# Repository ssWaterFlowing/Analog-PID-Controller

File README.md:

# Analog PID Controller
### A Fully Analog Closed-Loop LED Brightness Controller

## Project Overview

A **fully analog PID (Proportional-Integral-Derivative) controller** that regulates LED brightness using only op-amp circuits, passive components, and a BJT output driver. No microcontroller, no software, no digital processing. The system senses LED current, computes the error against a setpoint, and drives a corrective output through three parallel analog compensation paths (P, I, D) summed into a single control signal.

Designed as an independent project to physically realize classical control theory in hardware, where gain is set by resistor ratios, time constants by RC products, and stability by circuit topology.

**Authors:** Suren Shirani and Devansh Joshi

## System Architecture

The controller implements a standard closed-loop PID topology in five analog stages:

```
                         ┌──────────────────────────────────────────┐
                         │              PID Compensation            │
                         │                                          │
V_set ──┐                │  ┌─────────────┐                        │
        │  ┌───────────┐ │  │ Proportional │──┐                    │
        ├─►│ Difference ├─┼─►│   (Kp gain)  │  │  ┌─────────────┐  │  ┌────────────┐
        │  │ Amplifier  │ │  ├─────────────┤  ├─►│  Summing     ├──┼─►│  2N3904    ├──► LED
V_curr ─┘  │  (TL082)   │ │  │  Integral   │  │  │  Inverting   │  │  │  BJT       │
           └───────────┘ │  │  (Ki gain)   │──┘  │  Amplifier   │  │  │  Driver    │
              e(t)       │  ├─────────────┤      │  (TL084)     │  │  └────────────┘
                         │  │ Derivative   │──┘  └─────────────┘  │
                         │  │  (Kd gain)   │                       │
                         │  └─────────────┘                        │
                         │      (TL084)                            │
                         └──────────────────────────────────────────┘
                                                                    │
                         ┌──────────────────────────────────────────┘
                         │ Feedback: V_curr = f(I_LED)
                         └─────────────────────────────────────────►V_curr
```

### Signal Flow

1. **Setpoint (V_set):** A calculated reference voltage representing the desired LED operating point
2. **Current Sense (V_curr):** The LED forward voltage is measured directly as a proxy for LED current
3. **Error Computation:** A TL082 difference amplifier computes `e(t) = V_set − V_curr`
4. **PID Compensation:** The error signal is routed in parallel to three TL084-based op-amp stages:
   - **P stage** - Resistor-ratio gain provides immediate proportional correction
   - **I stage** - Op-amp integrator (RC time constant) accumulates past error to eliminate steady-state offset
   - **D stage** - Op-amp differentiator (RC time constant) responds to rate-of-change to reduce overshoot
5. **Summation:** A TL084 summing inverting amplifier combines the P, I, and D outputs into a single control voltage
6. **Output Driver:** A 2N3904 NPN BJT in emitter-follower configuration converts the low-power control signal into a current drive capable of sourcing 20-40 mA to the LED
7. **Feedback:** The resulting LED voltage feeds back to the difference amplifier, closing the loop

## Circuit Design

### Component Summary

| Component | Part | Quantity | Role |
|---|---|---|---|
| Dual Op-Amp | TL082CP | 1 (2 channels) | Difference amplifier (error computation) |
| Quad Op-Amp | TL084CN | 1 (4 channels) | P, I, D stages + summing amplifier |
| NPN BJT | 2N3904 | 1 | Emitter-follower output driver |
| Potentiometers | PV37W104C01B00 (100 kΩ) | 3 | Kp, Ki, Kd gain tuning |
| Resistors | 10 kΩ | 14 | Gain-setting, biasing, feedback networks |
| Resistor | 2.2 kΩ | 1 | Biasing / current limiting |
| Resistor | 1 MΩ | 1 | High-impedance feedback path |
| Resistor | 620 Ω | 1 | LED current-limiting resistor |
| Capacitors | 0.1 µF | 2 | Bypass / filtering |
| Capacitors | 1 µF | 2 | Integrator time constant |
| Capacitor | 220 nF | 1 | PID compensation |
| Capacitor | 2.7 nF | 1 | Differentiator time constant |
| Capacitor | 10 µF | 1 | Power supply bypass |
| LEDs | - | 2 | Controlled output LED + indicator |
| Test Points | - | 17 | Probing at every stage of the signal path |

### Op-Amp Stage Details

**Difference Amplifier (TL082):**
Computes the error signal `e(t) = V_set − V_curr` using matched 10 kΩ resistor pairs for unity differential gain. The TL082's JFET inputs provide high input impedance to avoid loading the sense node.

**Proportional Stage (TL084, Channel A):**
An inverting amplifier whose gain `Kp` is set by the ratio of a feedback resistor to the input resistor, with a PV37W104C01B00 potentiometer (100 kΩ) for real-time Kp adjustment.

**Integral Stage (TL084, Channel B):**
A Miller integrator with a capacitor (1 µF) in the feedback path. The time constant `τ_i = R × C` determines how aggressively past error is accumulated. A 100 kΩ potentiometer tunes Ki.

**Derivative Stage (TL084, Channel C):**
A differentiator with an input capacitor (2.7 nF) and feedback resistor. The time constant `τ_d = R × C` sets the sensitivity to the rate of error change. A 100 kΩ potentiometer tunes Kd. The small capacitance value limits high-frequency noise amplification.

**Summing Inverting Amplifier (TL084, Channel D):**
Combines the P, I, and D outputs through input resistors into a single inverted control signal, which is then fed to the BJT driver.

### Output Driver

A **2N3904 NPN transistor** in emitter-follower (common-collector) configuration provides current gain to drive the LED at 20-40 mA. The emitter-follower topology offers:
- Near-unity voltage gain with high current gain (β ≈ 100-300)
- Low output impedance for stable LED drive
- Voltage-controlled current source (VCCS) behavior through the feedback loop

### Test Points

17 test points are distributed across the signal path for oscilloscope probing at every critical node:

| Test Point | Node | Purpose |
|---|---|---|
| TP_Vset | Setpoint voltage | Verify reference level |
| TP_Vcurr | Sensed LED voltage | Verify feedback signal |
| TP_Error_output | Difference amp output | Verify e(t) computation |
| TP_PID_error_input | PID stage input | Confirm error signal routing |
| TP_P_Vn_amp | P stage output | Verify proportional response |
| TP_I_Vn_amp | I stage output | Verify integrator behavior |
| TP_D_Vn_amp | D stage output | Verify differentiator response |
| TP_Summing_Amp_Vn | Summing amp output | Verify combined PID signal |
| TP_BJT_Base | BJT base | Verify driver input |
| TP_Vcc | Supply rail | Monitor supply stability |
| GND TPs | Ground references | Differential probe anchors |

## PCB Design

- **EDA Tool:** KiCad
- Full schematic capture with hierarchical net labels for signal tracing
- Custom PCB layout with dedicated analog ground plane for noise isolation
- Clean routing to minimize crosstalk between the high-impedance integrator/differentiator stages and the power output stage
- Custom footprint libraries created for the TL082CP, TL084CN, 2N3904, and PV37W104C01B00

## Testing & Validation

The controller is validated using standard bench equipment:

- **Oscilloscope:** Capture transient response (step input) and steady-state waveforms at each test point
- **Function Generator:** Inject controlled step and sinusoidal error signals to characterize P, I, and D responses independently
- **DC Power Supply:** Provide regulated supply voltage

### Performance Metrics

| Metric | Description |
|---|---|
| Rise Time | Time for output to reach 90% of setpoint after a step input |
| Overshoot | Peak deviation above setpoint (indicates D-stage tuning quality) |
| Settling Time | Time to stay within ±2% of setpoint |
| Steady-State Error | Residual offset after settling (should approach zero with I-stage) |
| Stability | Absence of sustained oscillation under varying gain settings |

All measurements are taken directly from hardware - not simulation alone.

## Project Structure

```
Analog-PID-Controller/
├── README.md
├── LICENSE
├── simpleDesignIdea.png              Hand-drawn system block diagram
│
├── AnalogPIDController/              KiCad project files
│   ├── AnalogPIDController.kicad_sch     Full schematic
│   ├── AnalogPIDController.kicad_pcb     PCB layout
│   ├── AnalogPIDController.kicad_pro     Project configuration
│   ├── AnalogPIDController.kicad_prl     Project settings
│   └── AnalogPIDController-backups/      Timestamped design backups
│
└── Additional Footprints/            Custom component libraries
    ├── 2N3904/                       NPN BJT symbol + footprint + 3D model
    ├── PV37W104C01B00/               100 kΩ trimmer potentiometer
    ├── TL082CP/                      Dual JFET op-amp
    └── TL084CN/                      Quad JFET op-amp
```

## Authors

**Devansh Joshi** - [GitHub](https://github.com/devanshjoshi08)

**Suren Shirani** - [GitHub](https://github.com/ssWaterFlowing)

## License

This project is licensed under the [MIT License](LICENSE).

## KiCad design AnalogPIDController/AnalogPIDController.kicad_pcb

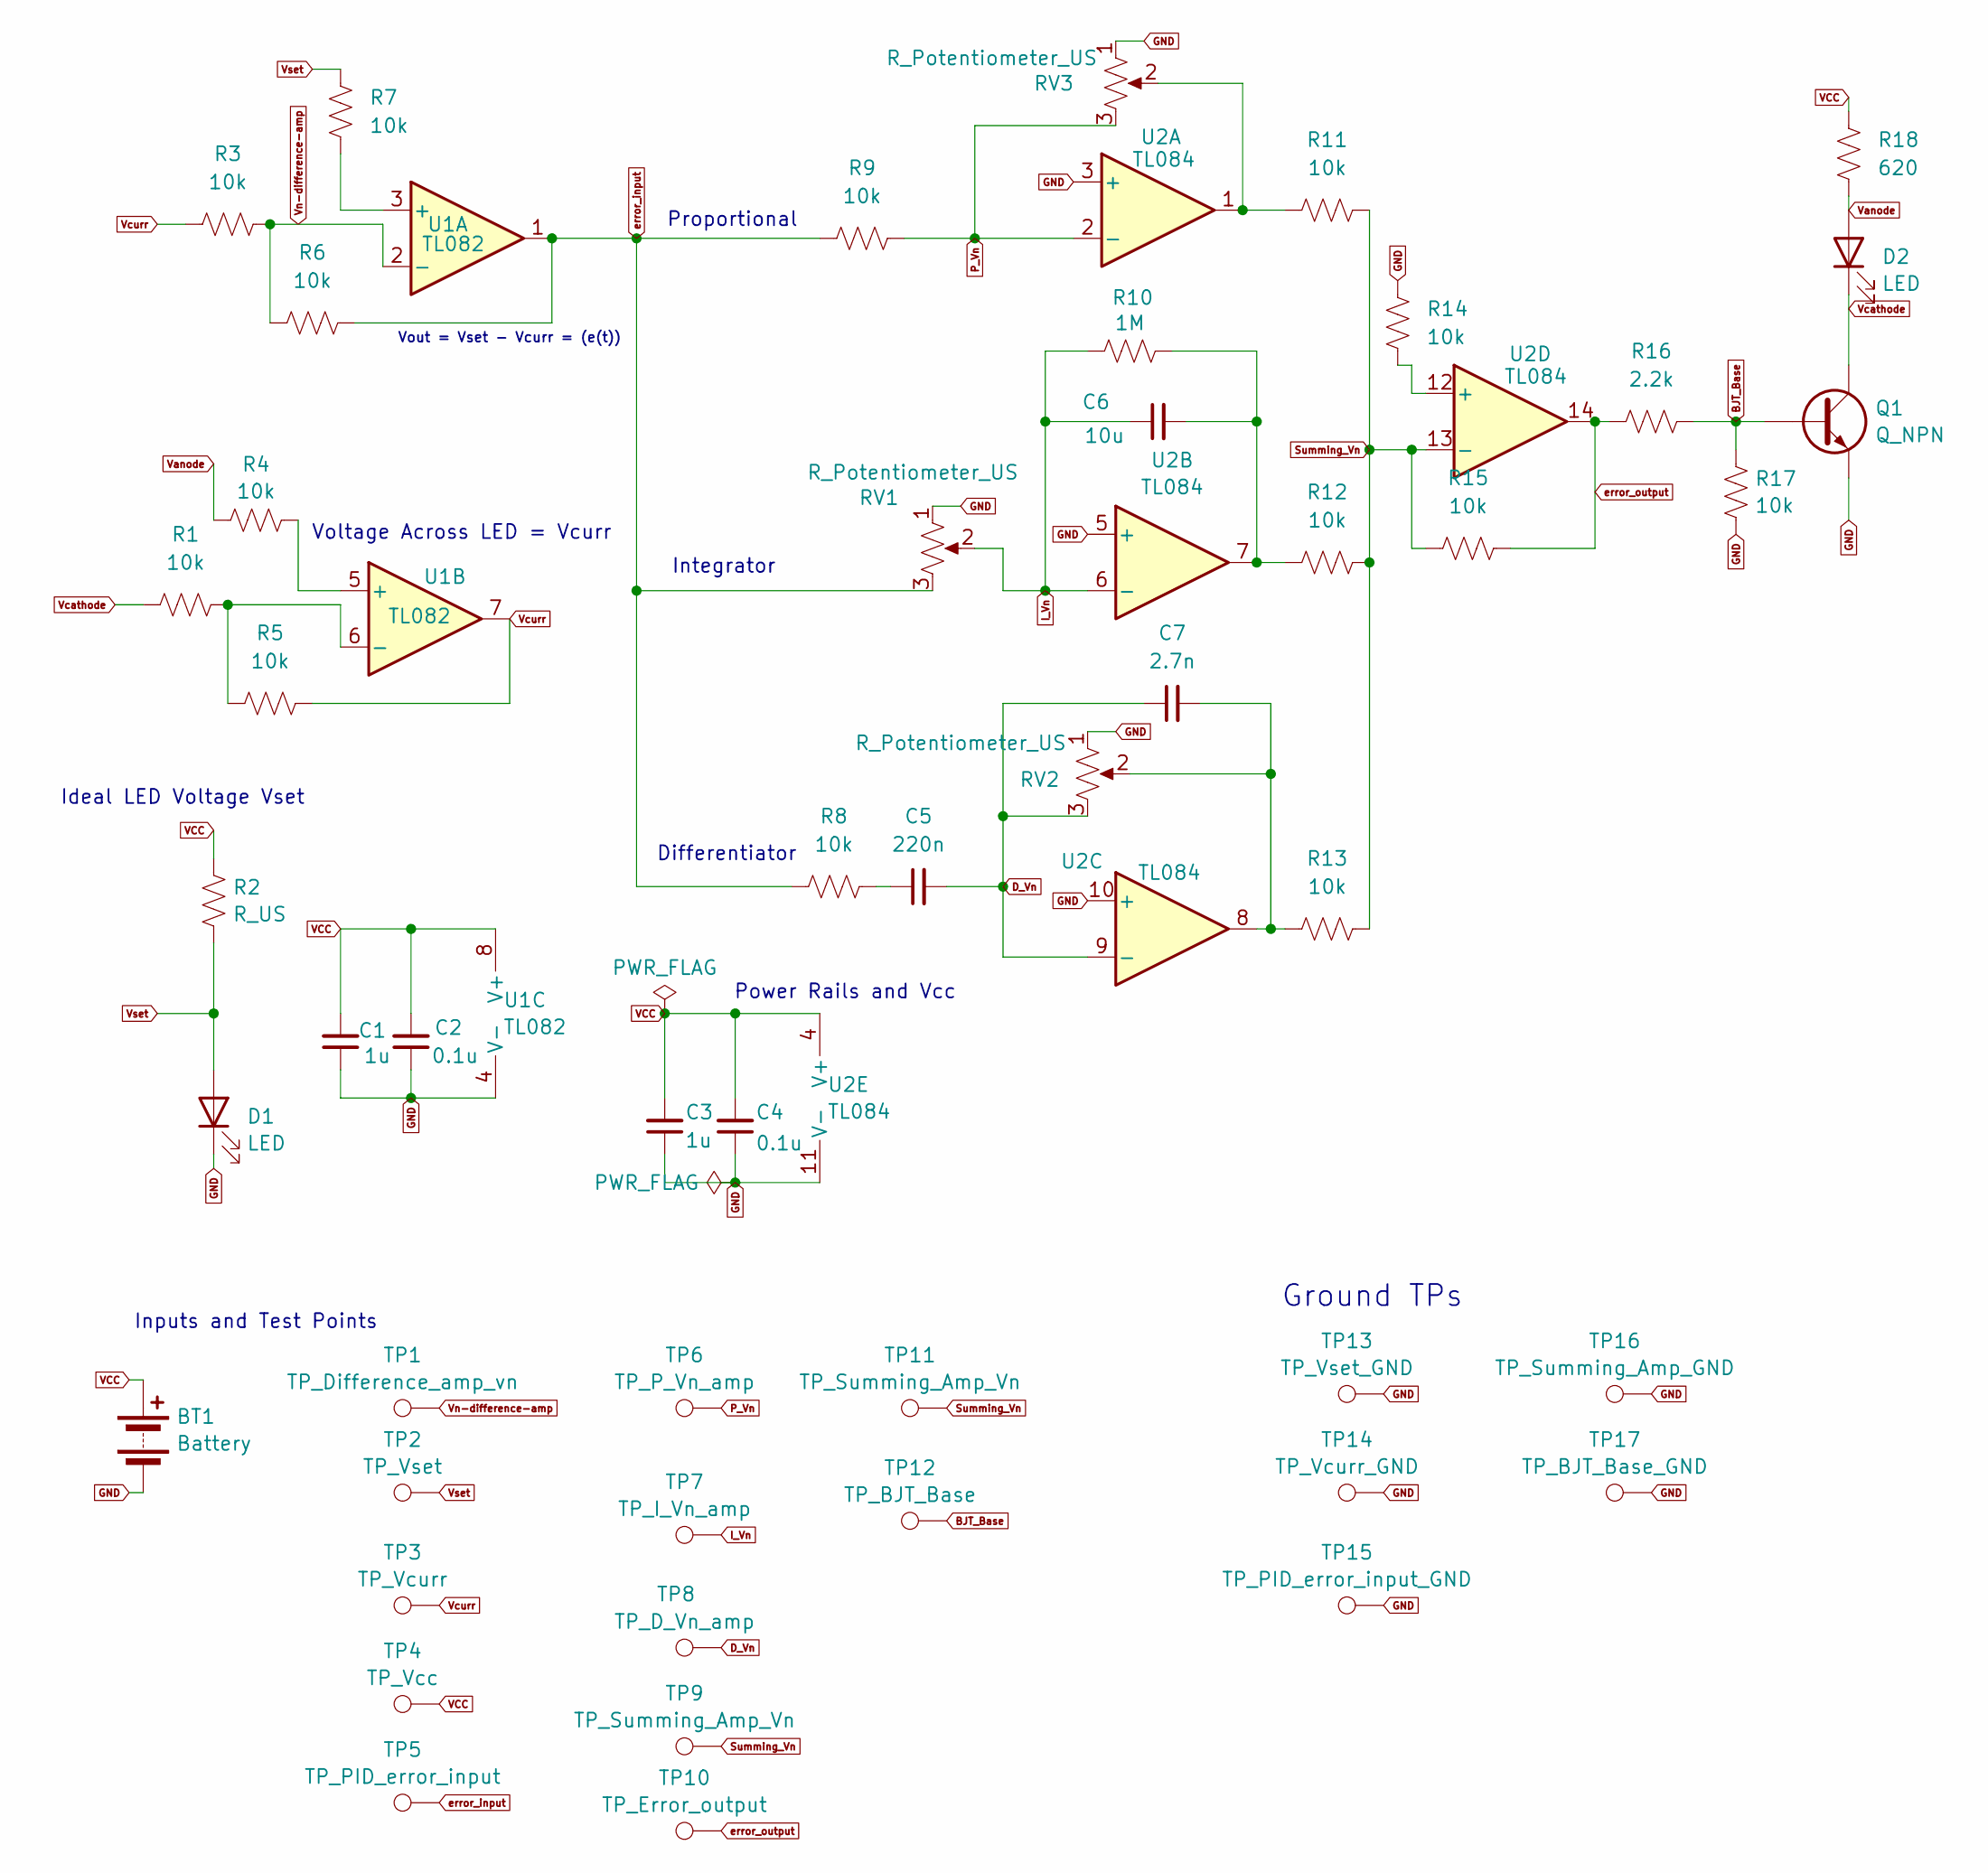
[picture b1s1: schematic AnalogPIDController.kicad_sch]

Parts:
BT1: Battery; TerminalBlock_Phoenix_MKDS-1,5-2-5.08_1x02_P5.08mm_Horizont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
C1, C3: 1u; C_Disc_D3.8mm_W2.6mm_P2.50mm
C2, C4: 0.1u; C_Disc_D3.8mm_W2.6mm_P2.50mm
C5: 220n; C_Disc_D3.8mm_W2.6mm_P2.50mm
C6: 10u; C_Disc_D3.8mm_W2.6mm_P2.50mm
C7: 2.7n; C_Disc_D3.8mm_W2.6mm_P2.50mm
D1, D2: LED; LED_D1.8mm_W1.8mm_H2.4mm_Horizontal_O6.35mm_Z4.9mm
Q1: Q_NPN; TO92254P460H750-3
R1, R3, R4, R5, R6, R7, R8, R9, R11, R12, R13, R14, R15, R17: 10k; R_Axial_DIN0207_L6.3mm_D2.5mm_P10.16mm_Horizontal
R2: R_US; R_Axial_DIN0207_L6.3mm_D2.5mm_P10.16mm_Horizontal
R10: 1M; R_Axial_DIN0207_L6.3mm_D2.5mm_P10.16mm_Horizontal
R16: 2.2k; R_Axial_DIN0207_L6.3mm_D2.5mm_P10.16mm_Horizontal
R18: 620; R_Axial_DIN0207_L6.3mm_D2.5mm_P10.16mm_Horizontal
RV1, RV2, RV3: R_Potentiometer_US; TRIM_PV37W104C01B00
TP1: TP_Difference_amp_vn; TestPoint_Keystone_5010-5014_Multipurpose
TP2: TP_Vset; TestPoint_Keystone_5010-5014_Multipurpose
TP3: TP_Vcurr; TestPoint_Keystone_5010-5014_Multipurpose
TP4: TP_Vcc; TestPoint_Keystone_5010-5014_Multipurpose
TP5: TP_PID_error_input; TestPoint_Keystone_5010-5014_Multipurpose
TP6: TP_P_Vn_amp; TestPoint_Keystone_5010-5014_Multipurpose
TP7: TP_I_Vn_amp; TestPoint_Keystone_5010-5014_Multipurpose
TP8: TP_D_Vn_amp; TestPoint_Keystone_5010-5014_Multipurpose
TP9, TP11: TP_Summing_Amp_Vn; TestPoint_Keystone_5010-5014_Multipurpose
TP10: TP_Error_output; TestPoint_Keystone_5010-5014_Multipurpose
TP12: TP_BJT_Base; TestPoint_Keystone_5010-5014_Multipurpose
TP13: TP_Vset_GND; TestPoint_Keystone_5010-5014_Multipurpose
TP14: TP_Vcurr_GND; TestPoint_Keystone_5010-5014_Multipurpose
TP15: TP_PID_error_input_GND; TestPoint_Keystone_5010-5014_Multipurpose
TP16: TP_Summing_Amp_GND; TestPoint_Keystone_5010-5014_Multipurpose
TP17: TP_BJT_Base_GND; TestPoint_Keystone_5010-5014_Multipurpose
U1: TL082; DIP794W45P254L959H508Q8
U2: TL084; DIP794W45P254L1969H508Q14

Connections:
BJT_Base: Q1.B, R16.2, R17.1, TP12.1
D_Vn: C5.2, C7.1, RV2.3, TP8.1, U2.9 (-)
GND: BT1.2 (-), C1.1, C2.1, C3.1, C4.1, D1.1 (K), Q1.E, R14.2, R17.2, RV1.1, RV2.1, RV3.1, TP13.1, TP14.1, TP15.1, TP16.1, TP17.1, U1.4 (V-), U2.3 (+), U2.5 (+), U2.10 (+), U2.11 (V-)
I_Vn: C6.1, R10.1, RV1.2, TP7.1, U2.6 (-)
unnamed: C5.1, R8.2
unnamed: C6.2, R10.2, R12.1, U2.7
unnamed: C7.2, R13.1, RV2.2, U2.8
unnamed: R11.1, RV3.2, U2.1
unnamed: R7.1, U1.3 (+)
unnamed: R4.1, U1.5 (+)
unnamed: R1.2, R5.2, U1.6 (-)
unnamed: R14.1, U2.12 (+)
P_Vn: R9.2, RV3.3, TP6.1, U2.2 (-)
Summing_Vn: R11.2, R12.2, R13.2, R15.1, TP9.1, TP11.1, U2.13 (-)
VCC: BT1.1 (+), C1.2, C2.2, C3.2, C4.2, R2.1, R18.2, TP4.1, U1.8 (V+), U2.4 (V+)
Vanode: D2.2 (A), R4.2, R18.1
Vcathode: D2.1 (K), Q1.C, R1.1
Vcurr: R3.1, R5.1, TP3.1, U1.7
Vn-difference-amp: R3.2, R6.2, TP1.1, U1.2 (-)
Vset: D1.2 (A), R2.2, R7.2, TP2.1
error_input: R6.1, R8.1, R9.1, RV1.3, TP5.1, U1.1
error_output: R15.2, R16.1, TP10.1, U2.14

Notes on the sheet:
Proportional
Integrator
Voltage Across LED = Vcurr
Power Rails and Vcc
Vout = Vset - Vcurr = (e(t))
Differentiator
Ideal LED Voltage Vset
Inputs and Test Points
Ground TPs

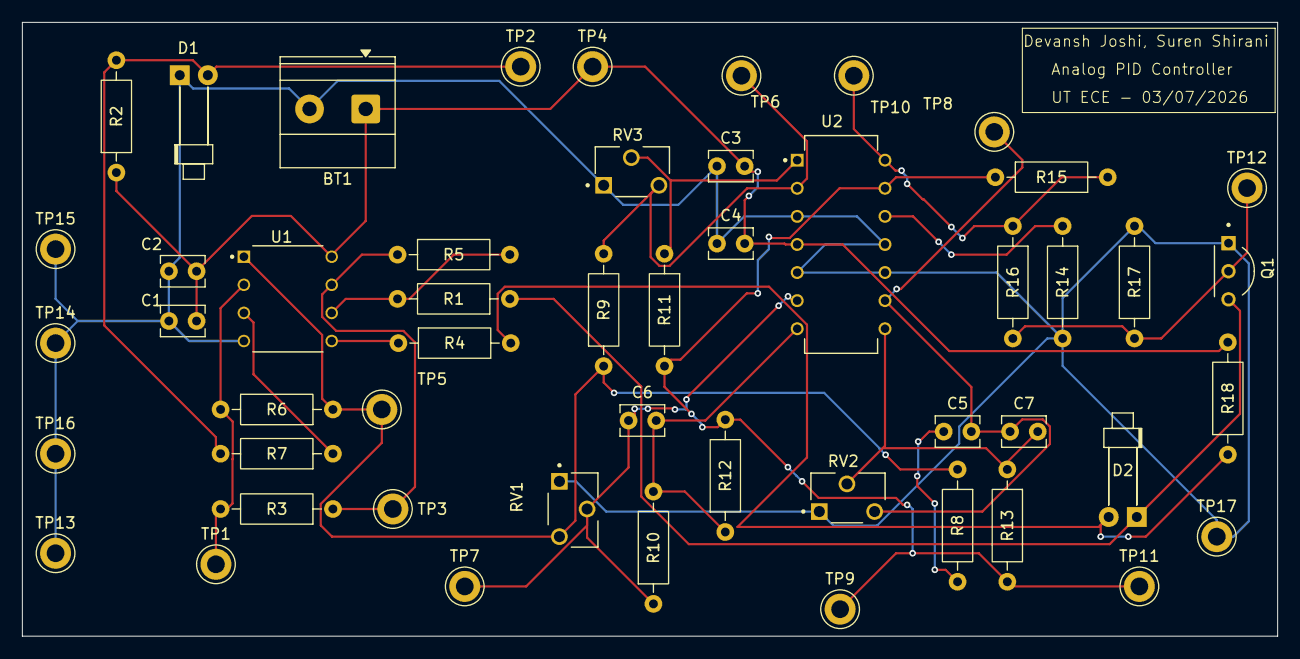
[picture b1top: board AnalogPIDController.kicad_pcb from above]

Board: 2 copper layers, 113.5 x 55.5 mm, 51 parts (0 on the bottom side), 22 nets.

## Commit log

2026-02-21 added
2026-02-21 Added image of simple design
2026-02-21 added Vcurr = Vled to image
2026-02-21 added diff amp
2026-02-21 added op amp
2026-02-21 Finished Some of PID schematic
2026-02-21 added inv summer along with pid
2026-02-21 fixed our idea, added transistor driver section, added some Vcurr led diff. amp circuit, and ideal LED voltage Vset
2026-02-21 Same as last commit
2026-02-21 stuff
2026-02-22 fixes
2026-02-22 Added testpoints and no erc errors rn
2026-02-22 Assigned some footprints
2026-02-22 added footprints
2026-02-22 assigned footprints, next step is to work on pcb wiring
2026-02-23 placing (w/o routing)
2026-03-07 adjustments to layout
2026-03-07 adjustments
2026-03-07 finished routing
2026-03-07 Finished PCb design, need to order pcb
2026-04-25 Update copyright holder in LICENSE file
2026-05-12 Rewrite README with full technical documentation
    Add detailed system architecture, signal flow, component summary
    with actual part numbers and values from the schematic, op-amp
    stage breakdowns, test point map, PCB design notes, and project
    structure.
2026-05-12 Add Suren's GitHub link to contributors
2026-05-12 Separate author lines in contributors
2026-05-12 Replace em dashes and en dashes with hyphens
